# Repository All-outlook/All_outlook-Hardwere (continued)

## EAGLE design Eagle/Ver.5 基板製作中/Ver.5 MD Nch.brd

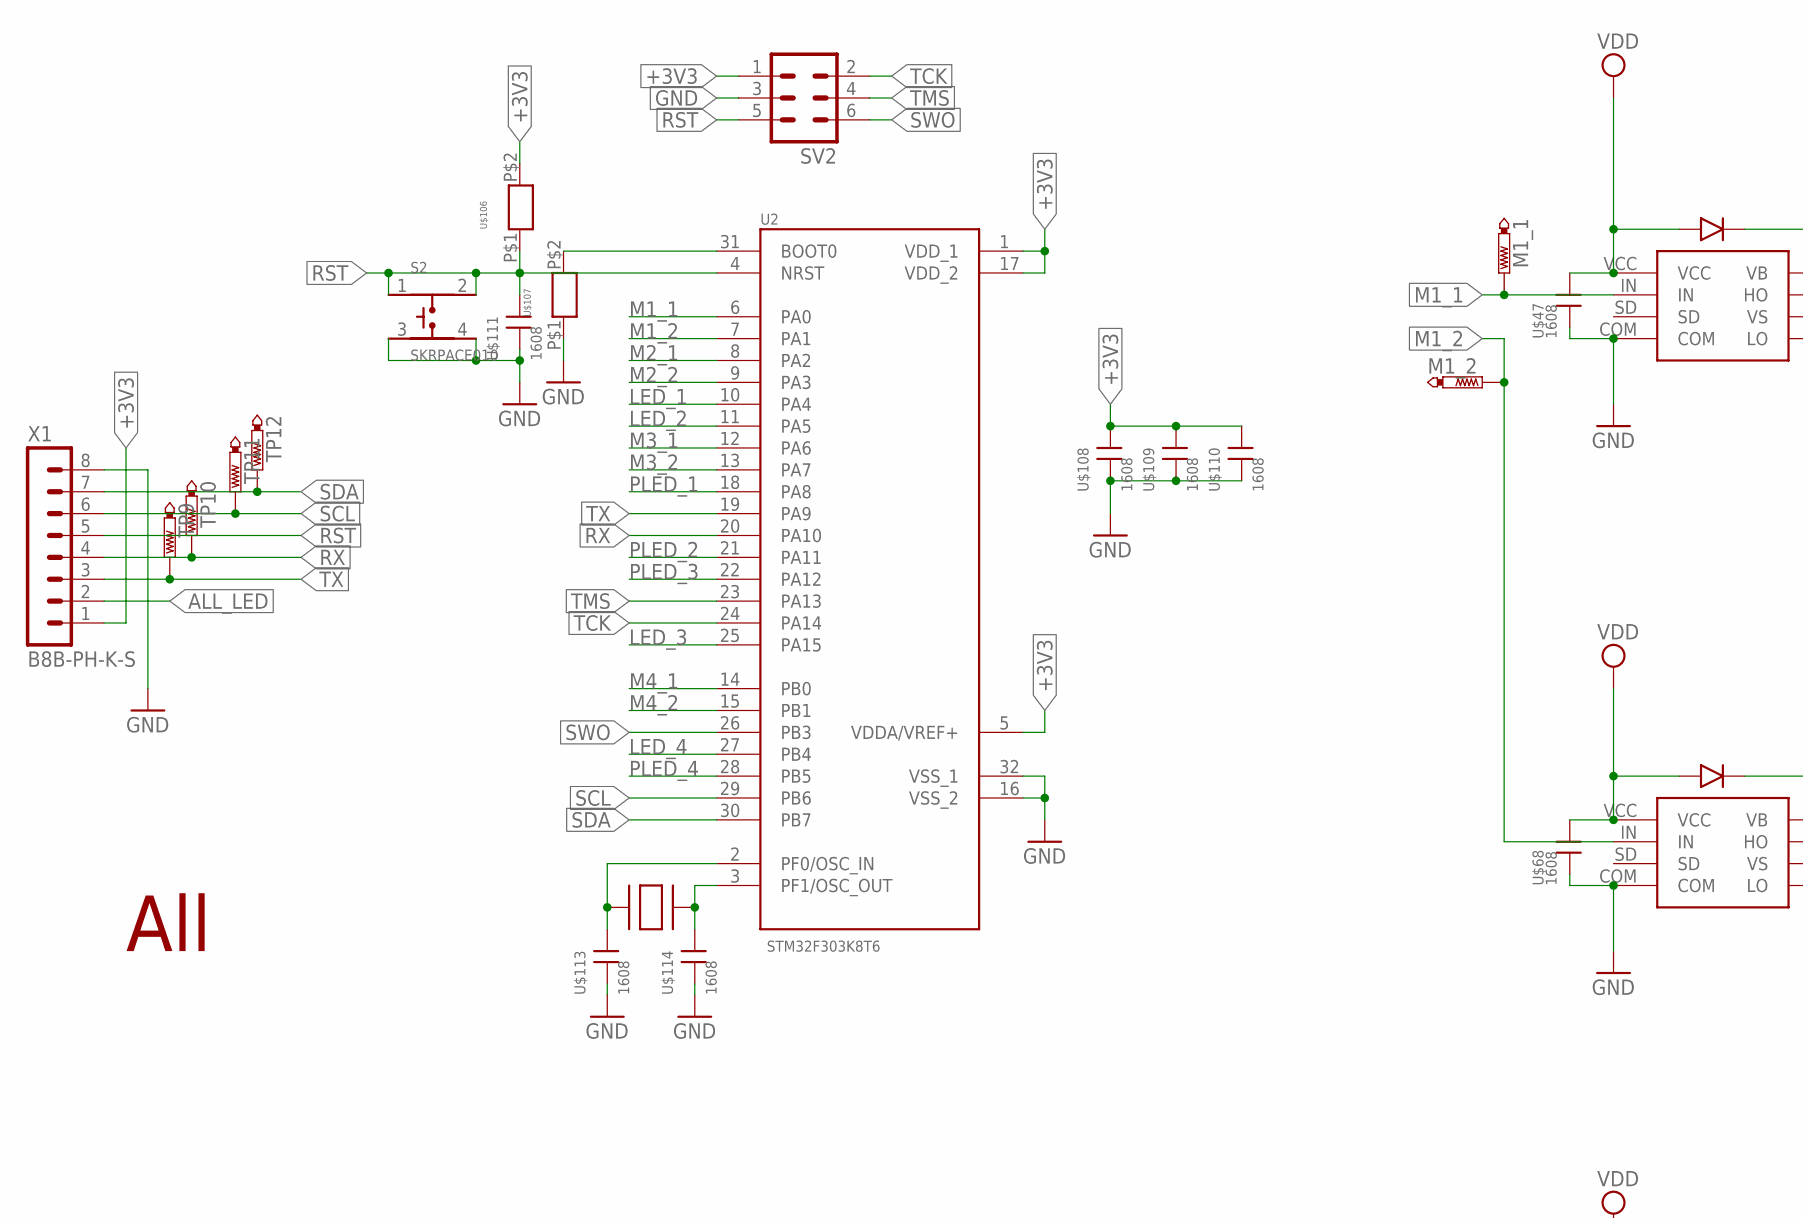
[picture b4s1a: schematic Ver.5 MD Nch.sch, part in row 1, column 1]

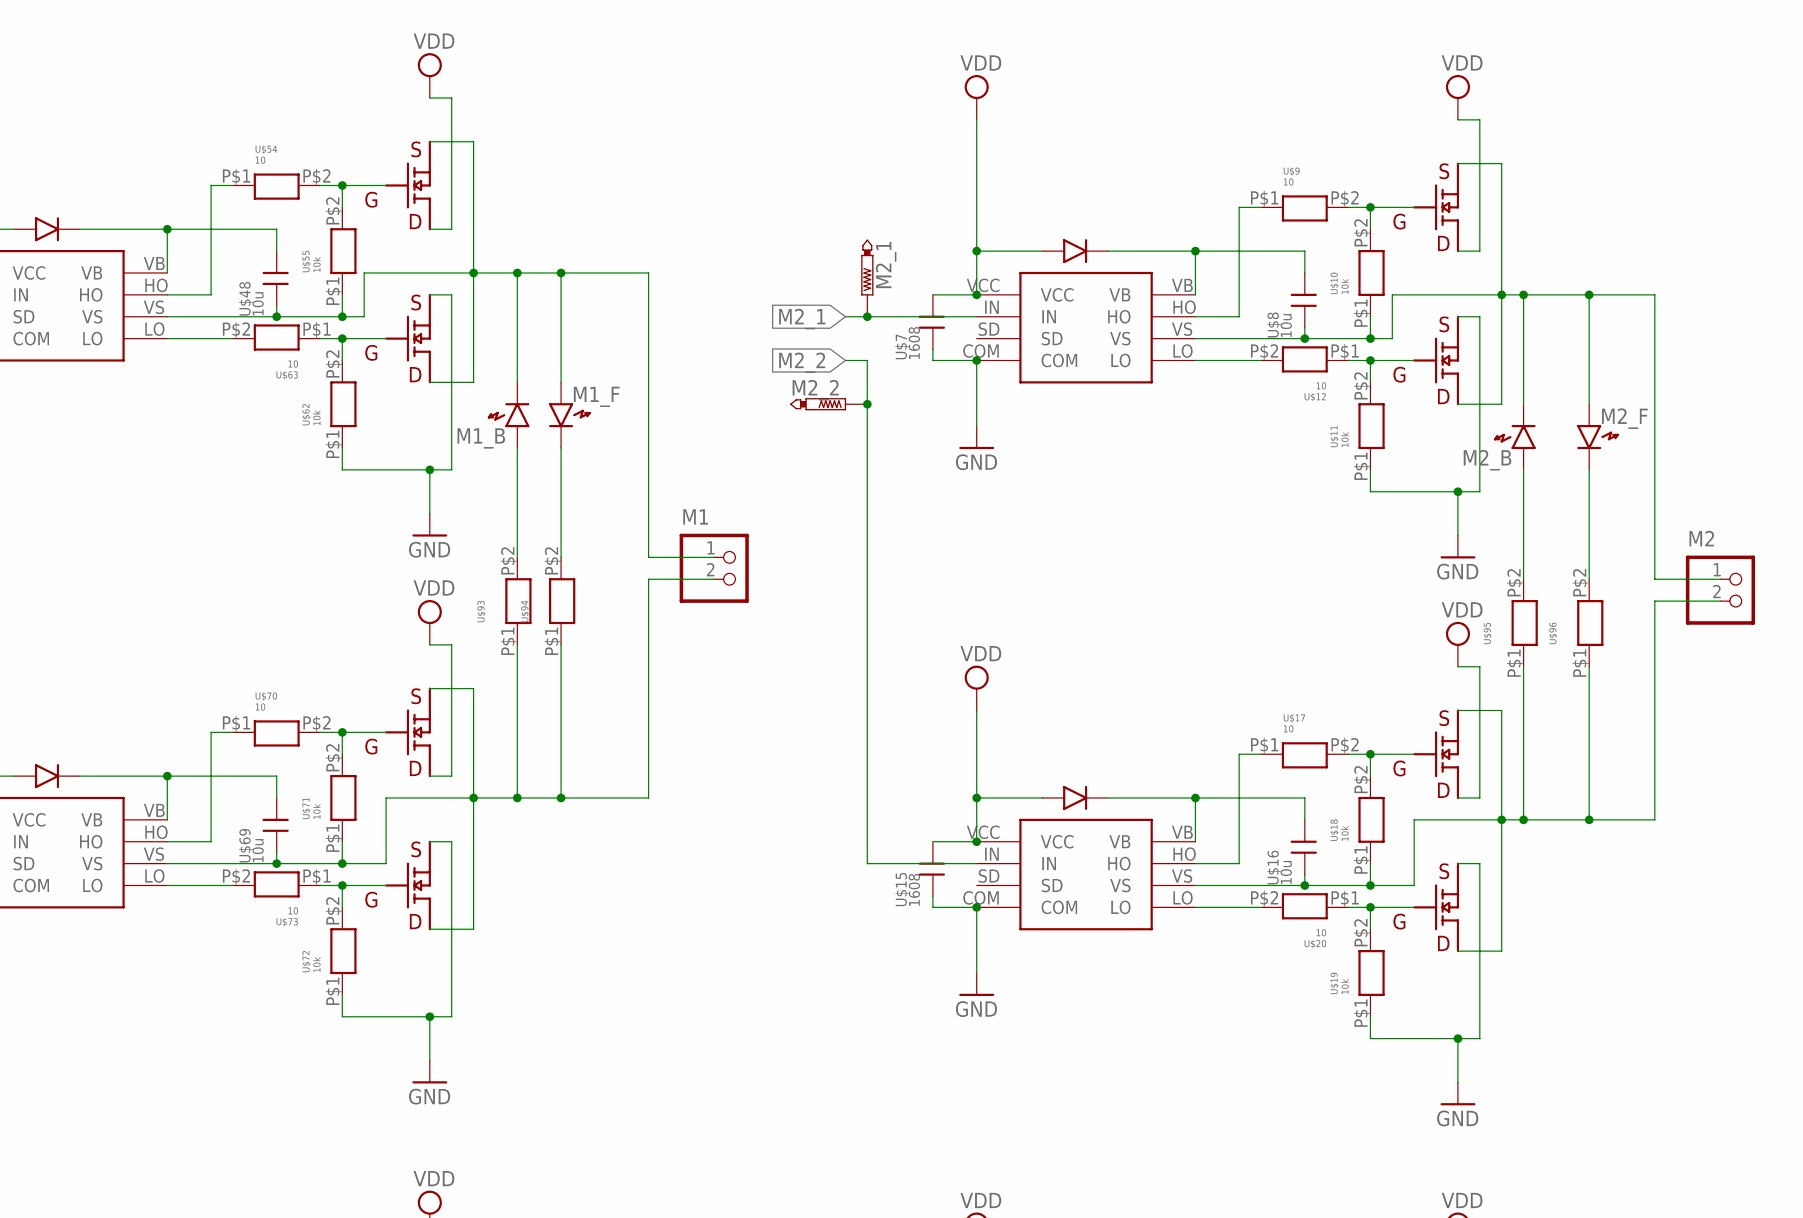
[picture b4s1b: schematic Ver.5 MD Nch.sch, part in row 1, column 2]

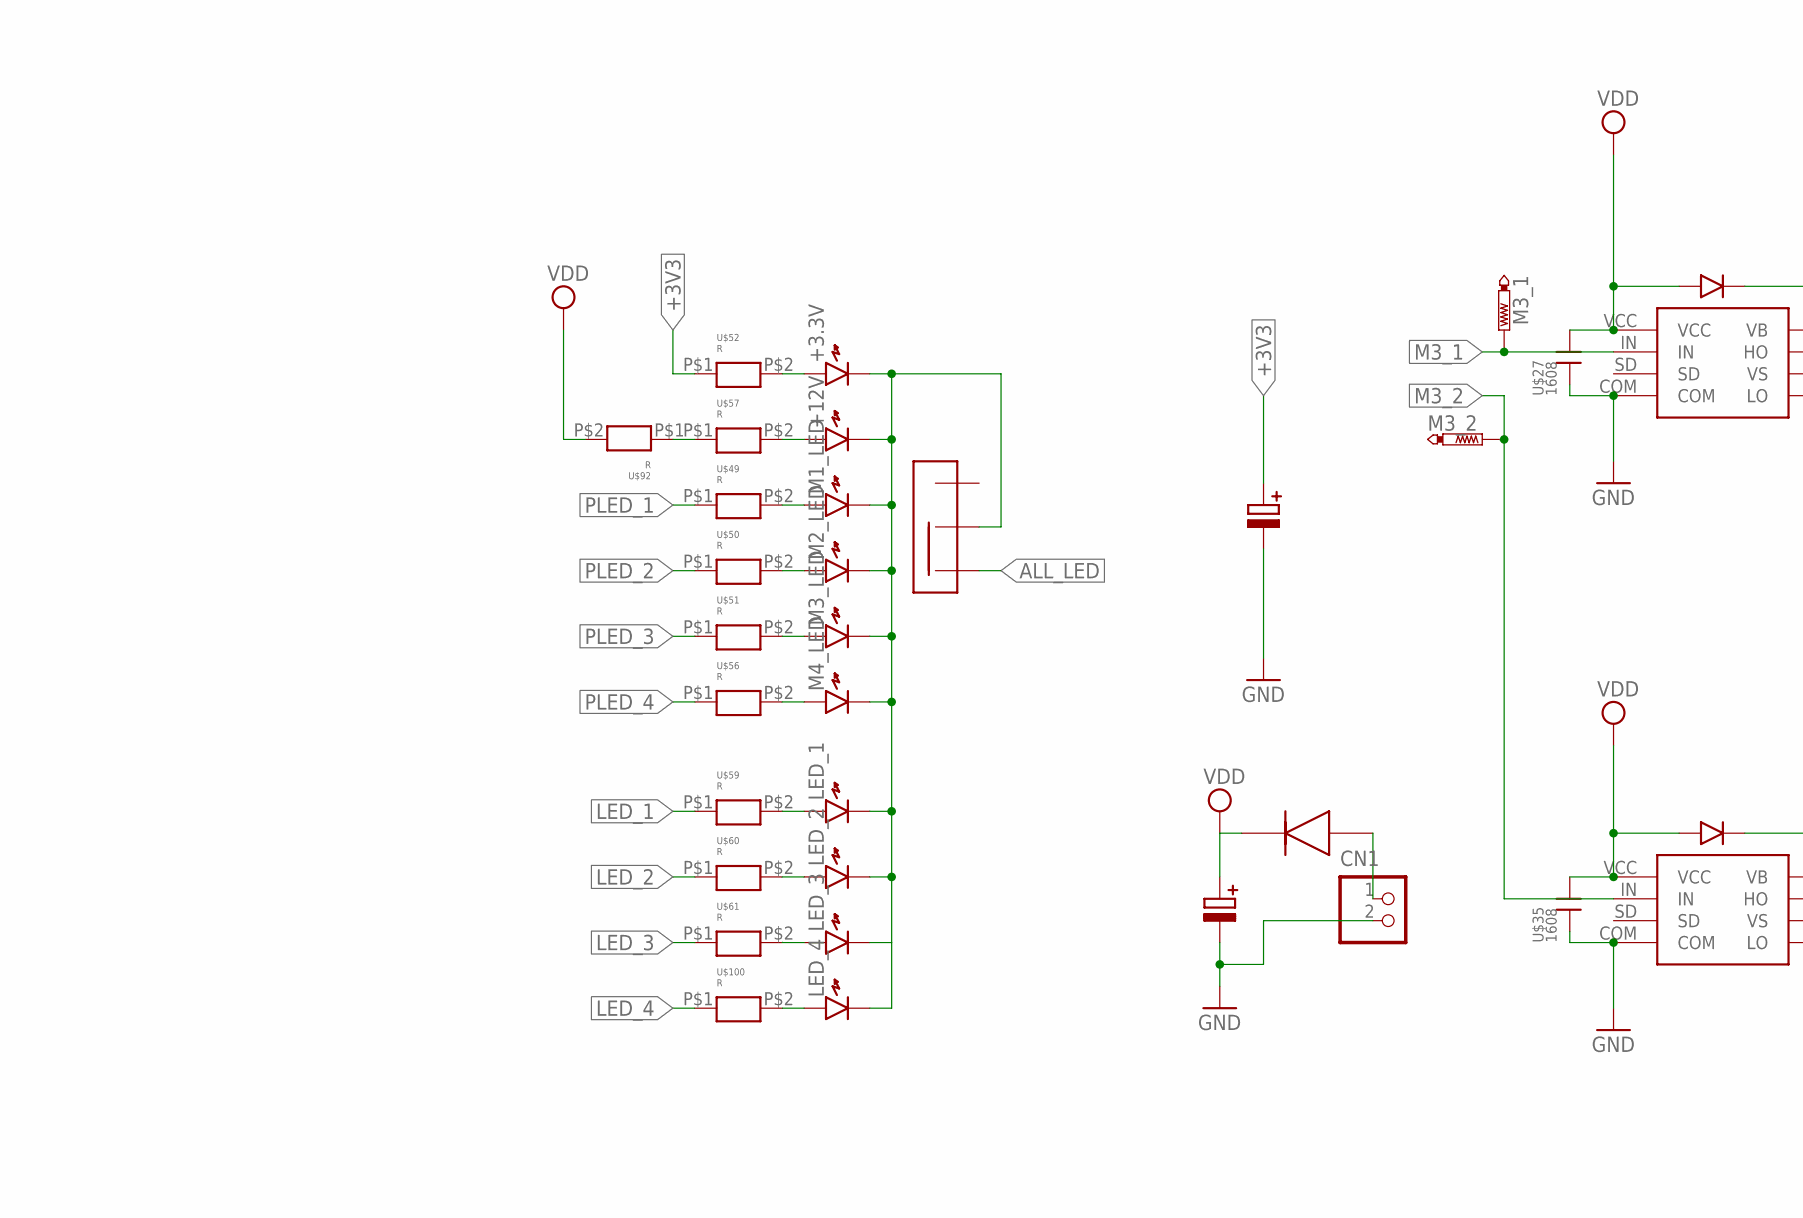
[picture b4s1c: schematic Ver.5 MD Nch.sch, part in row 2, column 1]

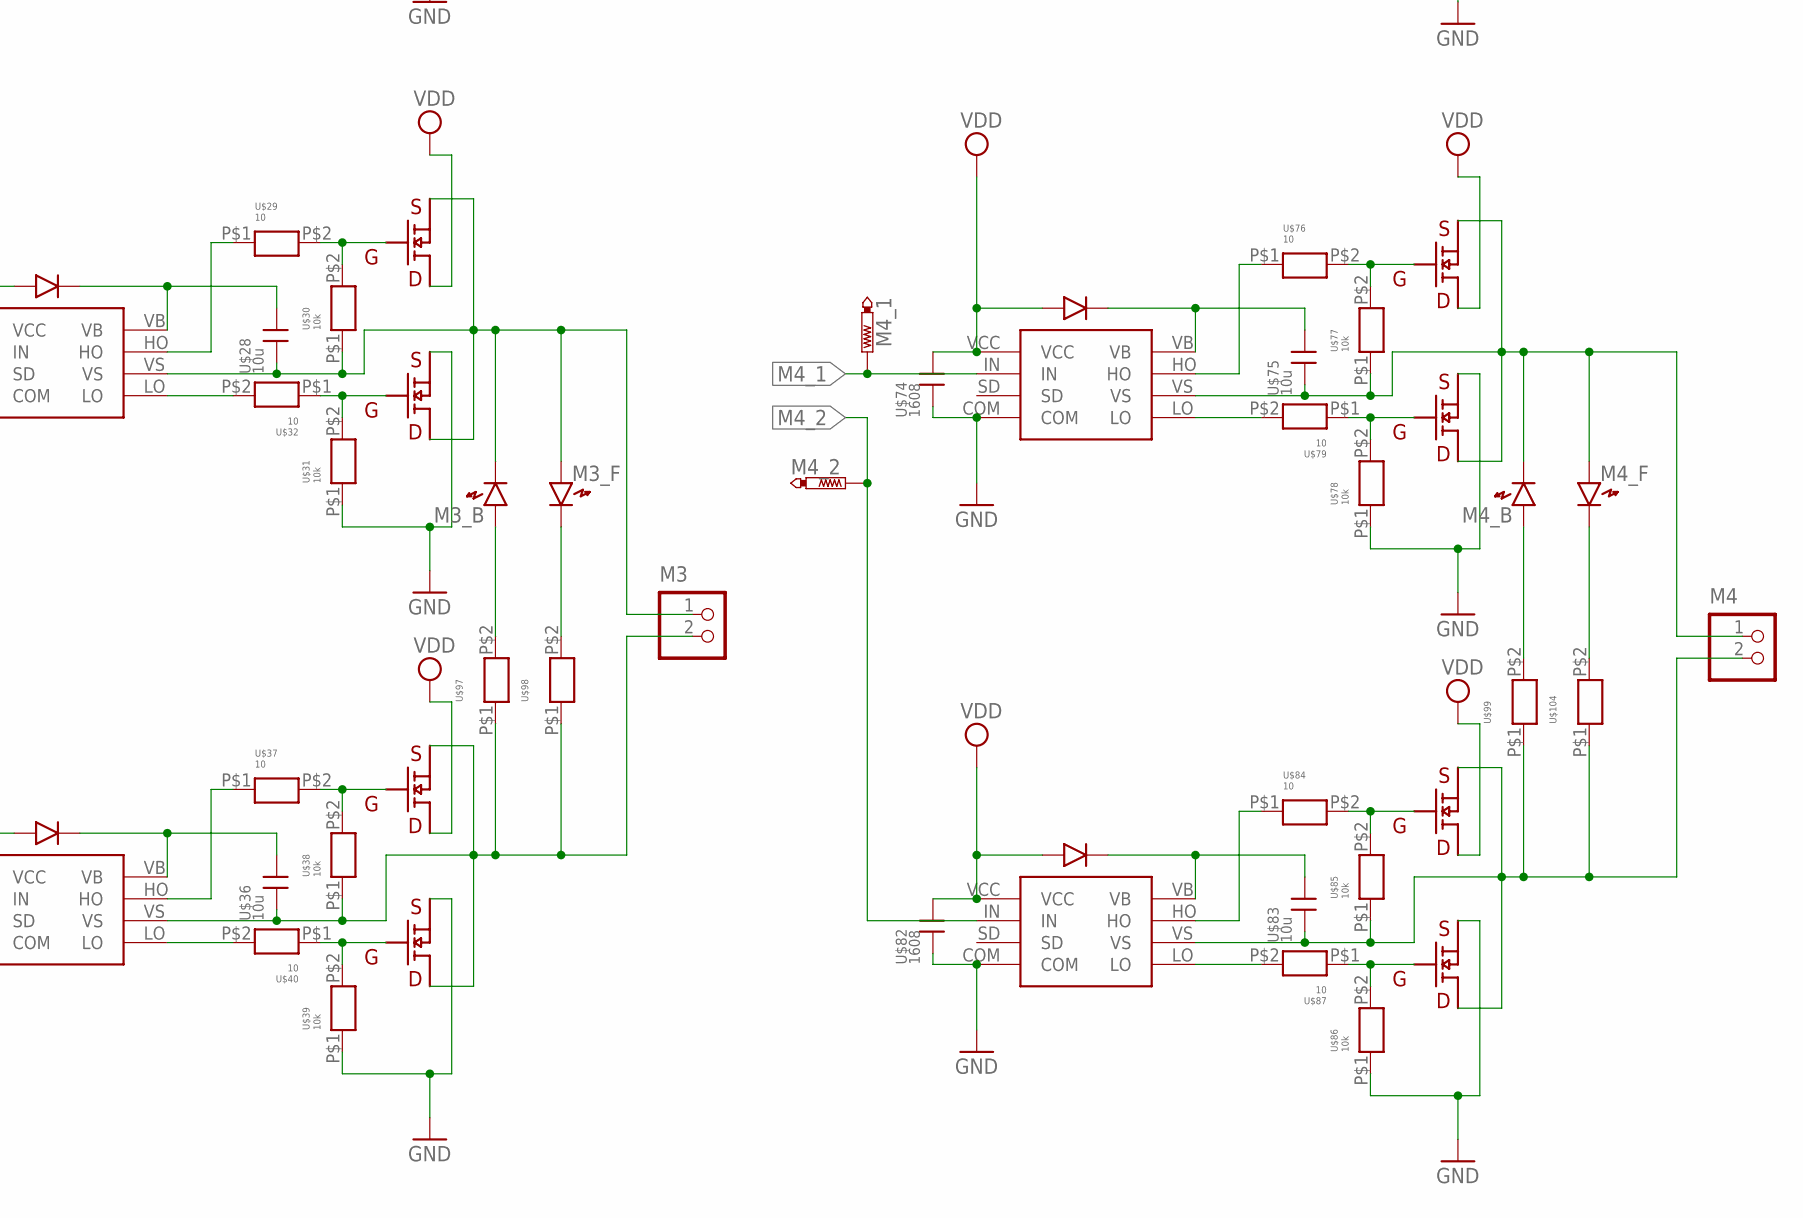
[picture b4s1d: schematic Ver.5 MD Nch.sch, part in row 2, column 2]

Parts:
+3.3V, +12V: LED1608
CN1: B2B-XH-A
LED_1, LED_2, LED_3, LED_4: LED1608
M1, M2, M3, M4: S2B-XH-A
M1_1, M1_2, M2_1, M2_2, M3_1, M3_2, M4_1, M4_2: PTR1B1,27; B1,27
M1_B, M1_F, M1_LED, M2_B, M2_F, M2_LED, M3_B, M3_F, M3_LED, M4_B, M4_F, M4_LED: LED1608
S2: SKRPACE010; SW_SKRPACE010
SV2: ML6
TP9, TP10, TP11, TP12: PTR1B1,27; B1,27
U2: STM32F303K8T6; QFP80P900X900X160-32N
U$1, U$2, U$3, U$4, U$21, U$22, U$23, U$24, U$41, U$42, U$43, U$44, U$88, U$89, U$90, U$91: SSM6K8
U$5, U$13, U$25, U$33, U$45, U$64, U$66, U$80: IR2302
U$6, U$14, U$26, U$34, U$46, U$65, U$67, U$81: 1N4148
U$7, U$15, U$27, U$35, U$47, U$68, U$74, U$82, U$108, U$109, U$110, U$111, U$113, U$114: 1608; CON
U$8, U$16, U$28, U$36, U$48, U$69, U$75, U$83: 10u; CON
U$9, U$12, U$17, U$20, U$29, U$32, U$37, U$40, U$54, U$63, U$70, U$73, U$76, U$79, U$84, U$87: 10; 1608
U$10, U$11, U$18, U$19, U$30, U$31, U$38, U$39, U$55, U$62, U$71, U$72, U$77, U$78, U$85, U$86: 10k; 1608
U$49, U$50, U$51, U$52, U$56, U$57, U$59, U$60, U$61, U$92, U$93, U$94, U$95, U$96, U$97, U$98, U$99, U$100, U$104, U$106, U$107: R; 1608
U$53: SSW
U$58, U$101: 25V100
U$102: 40V5A
U$103: ALL
U$112: SUISYOU; 水晶
X1: B8B-PH-K-S

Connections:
+3V3: SV2.1, U2.1 (VDD_1), U2.5 (VDDA/VREF+), U2.17 (VDD_2), U$52.P$1, U$58.P$1, U$106.P$2, U$108.P$1 (1), U$109.P$1 (1), U$110.P$1 (1), X1.1
ALL_LED: U$53.P$1, X1.2
GND: CN1.2, S2.3, S2.4, SV2.3, U2.16 (VSS_2), U2.32 (VSS_1), U$2.S, U$4.S, U$5.COM, U$7.P$2 (2), U$11.P$1, U$13.COM, U$15.P$2 (2), U$19.P$1, U$22.S, U$24.S, U$25.COM, U$27.P$2 (2), U$31.P$1, U$33.COM, U$35.P$2 (2), U$39.P$1, U$42.S, U$44.S, U$45.COM, U$47.P$2 (2), U$58.P$2, U$62.P$1, U$64.COM, U$66.COM, U$68.P$2 (2), U$72.P$1, U$74.P$2 (2), U$78.P$1, U$80.COM, U$82.P$2 (2), U$86.P$1, U$89.S, U$91.S, U$101.P$2, U$107.P$1, U$108.P$2 (2), U$109.P$2 (2), U$110.P$2 (2), U$111.P$2 (2), U$113.P$2 (2), U$114.P$2 (2), X1.8
LED_1: U2.10 (PA4), U$59.P$1
LED_2: U2.11 (PA5), U$60.P$1
LED_3: U2.25 (PA15), U$61.P$1
LED_4: U2.27 (PB4), U$100.P$1
M1_1: M1_1.TP, U2.6 (PA0), U$45.IN
M1_2: M1_2.TP, U2.7 (PA1), U$66.IN
M2_1: M2_1.TP, U2.8 (PA2), U$5.IN
M2_2: M2_2.TP, U2.9 (PA3), U$13.IN
M3_1: M3_1.TP, U2.12 (PA6), U$25.IN
M3_2: M3_2.TP, U2.13 (PA7), U$33.IN
M4_1: M4_1.TP, U2.14 (PB0), U$64.IN
M4_2: M4_2.TP, U2.15 (PB1), U$80.IN
unnamed: M1.2, U$3.S, U$4.D, U$4.DD (D), U$4.DDD (D), U$4.DDDD (D), U$66.VS, U$69.P$2 (2), U$71.P$1, U$93.P$1, U$94.P$1
unnamed: U$5.VB, U$6.P$2, U$8.P$1 (1)
unnamed: M2.1, M2_B.K, M2_F.A, U$5.VS, U$8.P$2 (2), U$10.P$1, U$21.S, U$22.D, U$22.DD (D), U$22.DDD (D), U$22.DDDD (D)
unnamed: U$9.P$2, U$10.P$2, U$21.G
unnamed: M1_LED.A, U$49.P$2
unnamed: U$5.HO, U$9.P$1
unnamed: U$5.LO, U$12.P$2
unnamed: U$11.P$2, U$12.P$1, U$22.G
unnamed: U$13.VB, U$14.P$2, U$16.P$1 (1)
unnamed: U$17.P$2, U$18.P$2, U$23.G
unnamed: U$13.HO, U$17.P$1
unnamed: U$13.LO, U$20.P$2
unnamed: U$19.P$2, U$20.P$1, U$24.G
unnamed: M2.2, U$13.VS, U$16.P$2 (2), U$18.P$1, U$23.S, U$24.D, U$24.DD (D), U$24.DDD (D), U$24.DDDD (D), U$95.P$1, U$96.P$1
unnamed: U$25.VB, U$26.P$2, U$28.P$1 (1)
unnamed: M3.1, M3_B.K, M3_F.A, U$25.VS, U$28.P$2 (2), U$30.P$1, U$41.S, U$42.D, U$42.DD (D), U$42.DDD (D), U$42.DDDD (D)
unnamed: U$29.P$2, U$30.P$2, U$41.G
unnamed: M2_LED.A, U$50.P$2
unnamed: U$25.HO, U$29.P$1
unnamed: U$25.LO, U$32.P$2
unnamed: M3_LED.A, U$51.P$2
unnamed: U$31.P$2, U$32.P$1, U$42.G
unnamed: U$33.VB, U$34.P$2, U$36.P$1 (1)
unnamed: U$37.P$2, U$38.P$2, U$43.G
unnamed: U$33.HO, U$37.P$1
unnamed: U$33.LO, U$40.P$2
unnamed: U$39.P$2, U$40.P$1, U$44.G
unnamed: +3.3V.A, U$52.P$2
unnamed: CN1.1, U$102.P$1
unnamed: +12V.A, U$57.P$2
unnamed: M3.2, U$33.VS, U$36.P$2 (2), U$38.P$1, U$43.S, U$44.D, U$44.DD (D), U$44.DDD (D), U$44.DDDD (D), U$97.P$1, U$98.P$1
unnamed: U$64.VB, U$65.P$2, U$75.P$1 (1)
unnamed: LED_1.A, U$59.P$2
unnamed: M4_LED.A, U$56.P$2
unnamed: U$45.VB, U$46.P$2, U$48.P$1 (1)
unnamed: M1.1, M1_B.K, M1_F.A, U$1.S, U$2.D, U$2.DD (D), U$2.DDD (D), U$2.DDDD (D), U$45.VS, U$48.P$2 (2), U$55.P$1
unnamed: LED_3.A, U$61.P$2
unnamed: LED_2.A, U$60.P$2
unnamed: U$1.G, U$54.P$2, U$55.P$2
unnamed: U$45.HO, U$54.P$1
unnamed: U$45.LO, U$63.P$2
unnamed: U$2.G, U$62.P$2, U$63.P$1
unnamed: U$66.VB, U$67.P$2, U$69.P$1 (1)
unnamed: M4.1, M4_B.K, M4_F.A, U$64.VS, U$75.P$2 (2), U$77.P$1, U$88.S, U$89.D, U$89.DD (D), U$89.DDD (D), U$89.DDDD (D)
unnamed: U$3.G, U$70.P$2, U$71.P$2
unnamed: U$66.HO, U$70.P$1
unnamed: U$66.LO, U$73.P$2
unnamed: U$4.G, U$72.P$2, U$73.P$1
unnamed: U$76.P$2, U$77.P$2, U$88.G
unnamed: U$64.HO, U$76.P$1
unnamed: U$64.LO, U$79.P$2
unnamed: U$78.P$2, U$79.P$1, U$89.G
unnamed: U$80.VB, U$81.P$2, U$83.P$1 (1)
unnamed: U$84.P$2, U$85.P$2, U$90.G
unnamed: U$80.HO, U$84.P$1
unnamed: U$80.LO, U$87.P$2
unnamed: U$86.P$2, U$87.P$1, U$91.G
unnamed: M4.2, U$80.VS, U$83.P$2 (2), U$85.P$1, U$90.S, U$91.D, U$91.DD (D), U$91.DDD (D), U$91.DDDD (D), U$99.P$1, U$104.P$1
unnamed: U$57.P$1, U$92.P$1
unnamed: M1_B.A, U$93.P$2
unnamed: M1_F.K, U$94.P$2
unnamed: M2_B.A, U$95.P$2
unnamed: +3.3V.K, +12V.K, LED_1.K, LED_2.K, LED_3.K, LED_4.K, M1_LED.K, M2_LED.K, M3_LED.K, M4_LED.K, U$53.P$3
unnamed: LED_4.A, U$100.P$2
unnamed: M3_B.A, U$97.P$2
unnamed: M2_F.K, U$96.P$2
unnamed: M4_B.A, U$99.P$2
unnamed: M4_F.K, U$104.P$2
unnamed: M3_F.K, U$98.P$2
unnamed: U2.31 (BOOT0), U$107.P$2
unnamed: U2.2 (PF0/OSC_IN), U$112.P$1, U$113.P$1 (1)
unnamed: U2.3 (PF1/OSC_OUT), U$112.P$2, U$114.P$1 (1)
PLED_1: U2.18 (PA8), U$49.P$1
PLED_2: U2.21 (PA11), U$50.P$1
PLED_3: U2.22 (PA12), U$51.P$1
PLED_4: U2.28 (PB5), U$56.P$1
RST: S2.1, S2.2, SV2.5, U2.4 (NRST), U$106.P$1, U$111.P$1 (1), X1.5
RX: TP10.TP, U2.20 (PA10), X1.4
SCL: TP11.TP, U2.29 (PB6), X1.6
SDA: TP12.TP, U2.30 (PB7), X1.7
SWO: SV2.6, U2.26 (PB3)
TCK: SV2.2, U2.24 (PA14)
TMS: SV2.4, U2.23 (PA13)
TX: TP9.TP, U2.19 (PA9), X1.3
VDD: U$1.D, U$1.DD (D), U$1.DDD (D), U$1.DDDD (D), U$3.D, U$3.DD (D), U$3.DDD (D), U$3.DDDD (D), U$5.VCC, U$6.P$1, U$7.P$1 (1), U$13.VCC, U$14.P$1, U$15.P$1 (1), U$21.D, U$21.DD (D), U$21.DDD (D), U$21.DDDD (D), U$23.D, U$23.DD (D), U$23.DDD (D), U$23.DDDD (D), U$25.VCC, U$26.P$1, U$27.P$1 (1), U$33.VCC, U$34.P$1, U$35.P$1 (1), U$41.D, U$41.DD (D), U$41.DDD (D), U$41.DDDD (D), U$43.D, U$43.DD (D), U$43.DDD (D), U$43.DDDD (D), U$45.VCC, U$46.P$1, U$47.P$1 (1), U$64.VCC, U$65.P$1, U$66.VCC, U$67.P$1, U$68.P$1 (1), U$74.P$1 (1), U$80.VCC, U$81.P$1, U$82.P$1 (1), U$88.D, U$88.DD (D), U$88.DDD (D), U$88.DDDD (D), U$90.D, U$90.DD (D), U$90.DDD (D), U$90.DDDD (D), U$92.P$2, U$101.P$1, U$102.P$2

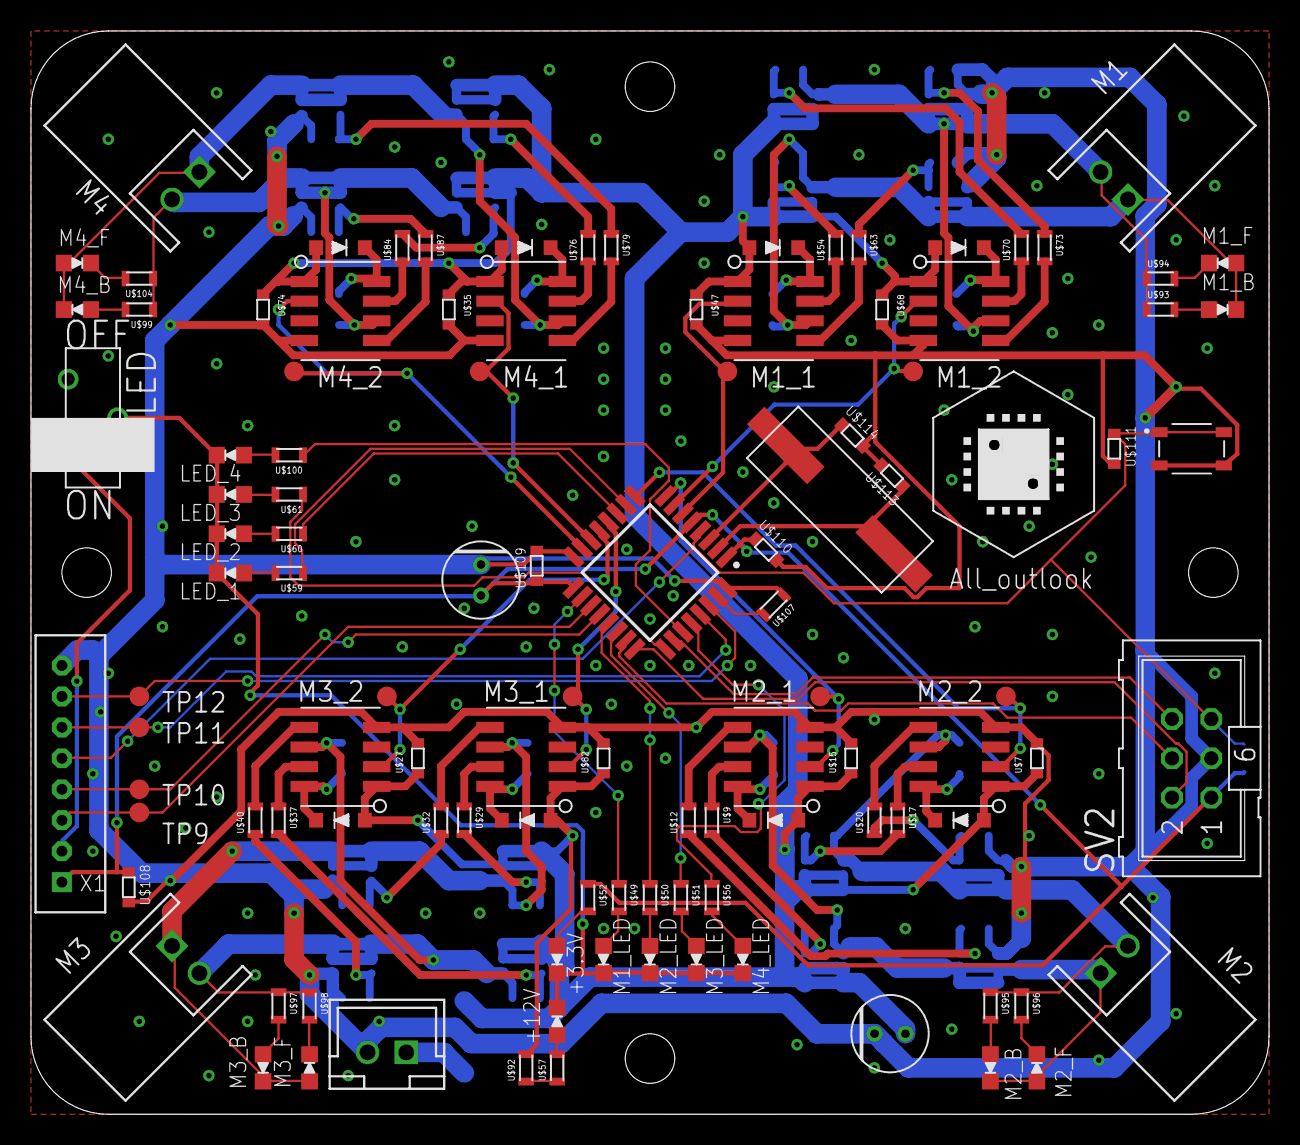
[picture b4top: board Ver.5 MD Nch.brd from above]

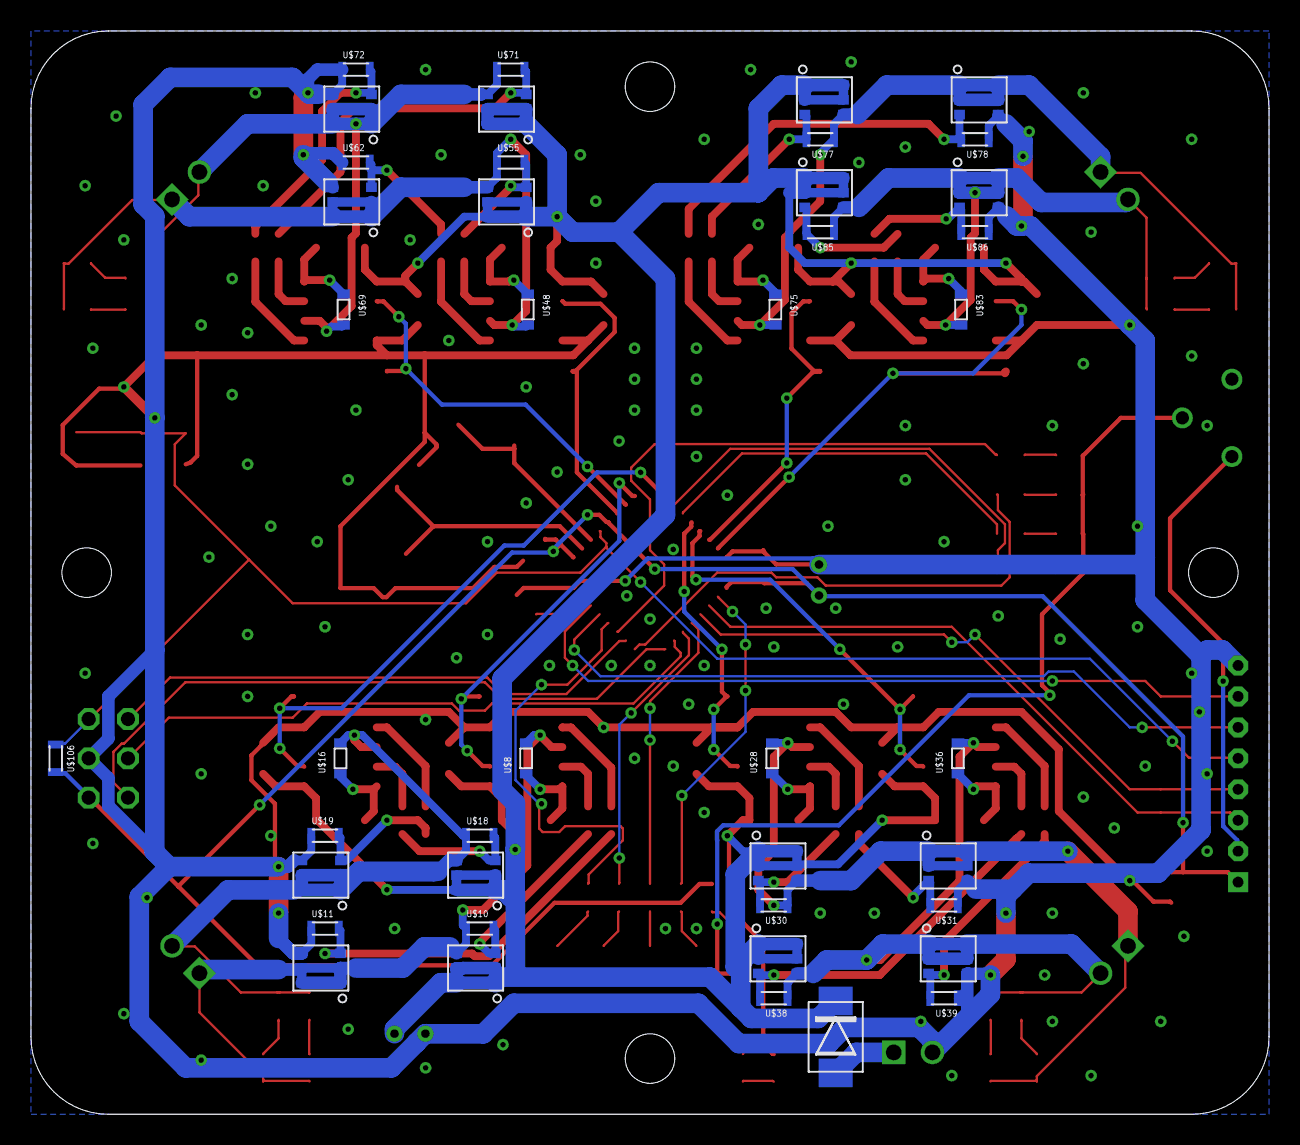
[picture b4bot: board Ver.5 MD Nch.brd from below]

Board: 2 copper layers, 80.0 x 70.0 mm, 152 parts (42 on the bottom side), 100 nets.

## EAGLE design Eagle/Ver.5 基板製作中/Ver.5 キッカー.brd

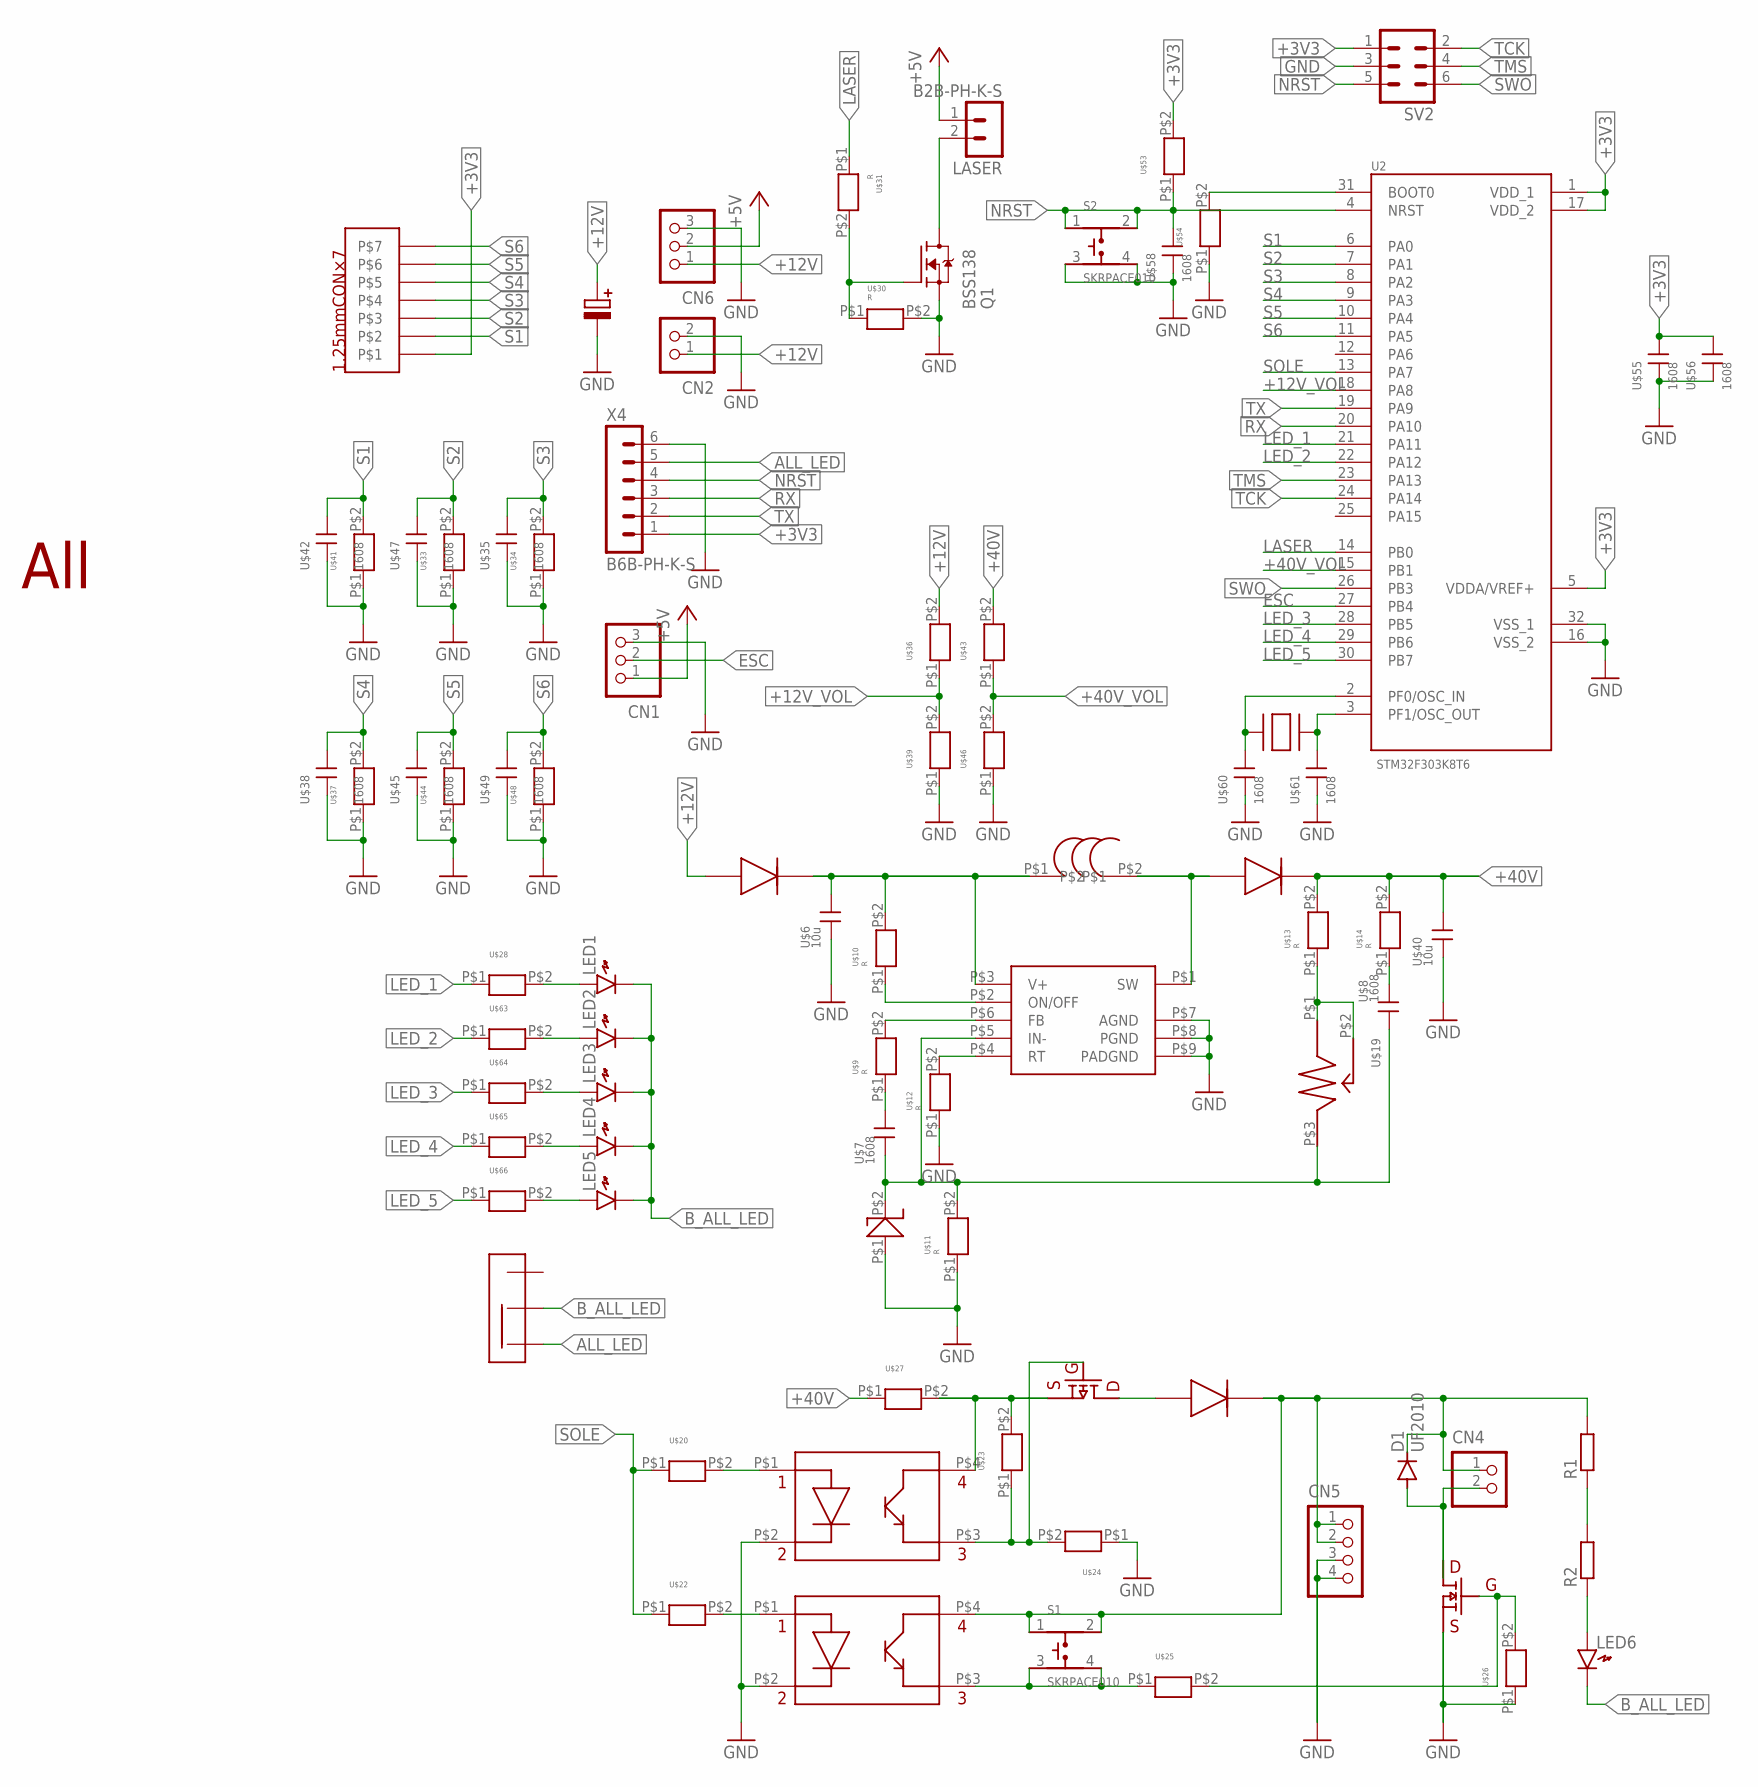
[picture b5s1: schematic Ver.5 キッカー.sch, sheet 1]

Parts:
CN1, CN6: B3B-XH-A
CN2, CN4: B2B-XH-A
CN5: B4B-XH-A
D1: UF2010; DO35-10
LASER: B2B-PH-K-S
LED1, LED2, LED3, LED4, LED5, LED6: LED1608
Q1: BSS138; SOT23
R1, R2: R-EU_0207/12; 0207/12
S1, S2: SKRPACE010; SW_SKRPACE010
SV2: ML6
U2: STM32F303K8T6; QFP80P900X900X160-32N
U$1: TD
U$2, U$3, U$18: 40V5A
U$4, U$15: TLP291; TPL291
U$5: NJW4131GM1; NJW4131
U$6, U$40: 10u; CON
U$7, U$8, U$35, U$38, U$42, U$45, U$47, U$49, U$55, U$56, U$58, U$60, U$61: 1608; CON
U$9, U$10, U$11, U$12, U$13, U$14, U$20, U$22, U$23, U$24, U$25, U$26, U$27, U$28, U$30, U$31, U$33, U$34, U$36, U$37, U$39, U$41, U$43, U$44, U$46, U$48, U$53, U$54, U$63, U$64, U$65, U$66: R; 1608
U$16: 808
U$17: SSM6K8
U$19: VR
U$21: 1MM7
U$29: ALL
U$50: I
U$59: SUISYOU; 水晶
U$62: 25V100
U$67: SSW
X4: B6B-PH-K-S

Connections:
+3V3: SV2.1, U2.1 (VDD_1), U2.5 (VDDA/VREF+), U2.17 (VDD_2), U$21.P$1, U$53.P$2, U$55.P$1 (1), U$56.P$1 (1), X4.1
+5V: CN1.1, CN6.2, LASER.1
+12V: CN2.1, CN6.1, U$3.P$1, U$36.P$2, U$62.P$1
+12V_VOL: U2.18 (PA8), U$36.P$1, U$39.P$2
+40V: U$2.P$2, U$13.P$2, U$14.P$2, U$27.P$1, U$40.P$1 (1), U$43.P$2
+40V_VOL: U2.15 (PB1), U$43.P$1, U$46.P$2
ALL_LED: U$67.P$1, X4.5
B_ALL_LED: LED1.K, LED2.K, LED3.K, LED4.K, LED5.K, LED6.K, U$67.P$3
ESC: CN1.2, U2.27 (PB4)
GND: CN1.3, CN2.2, CN5.3, CN5.4, CN6.3, Q1.2 (S), S2.3, S2.4, SV2.3, U2.16 (VSS_2), U2.32 (VSS_1), U$1.P$1, U$4.P$2 (2), U$5.P$7 (AGND), U$5.P$8 (PGND), U$5.P$9 (PADGND), U$6.P$2 (2), U$11.P$1, U$12.P$1, U$15.P$2 (2), U$17.S, U$24.P$1, U$26.P$1, U$30.P$2, U$33.P$1, U$34.P$1, U$35.P$2 (2), U$37.P$1, U$38.P$2 (2), U$39.P$1, U$40.P$2 (2), U$41.P$1, U$42.P$2 (2), U$44.P$1, U$45.P$2 (2), U$46.P$1, U$47.P$2 (2), U$48.P$1, U$49.P$2 (2), U$54.P$1, U$55.P$2 (2), U$56.P$2 (2), U$58.P$2 (2), U$60.P$2 (2), U$61.P$2 (2), U$62.P$2, X4.6
LASER: U2.14 (PB0), U$31.P$1
LED_1: U2.21 (PA11), U$28.P$1
LED_2: U2.22 (PA12), U$63.P$1
LED_3: U2.28 (PB5), U$64.P$1
LED_4: U2.29 (PB6), U$65.P$1
LED_5: U2.30 (PB7), U$66.P$1
unnamed: U$4.P$1 (1), U$20.P$2
unnamed: U$5.P$2 (ON/OFF), U$10.P$1
unnamed: U$1.P$2, U$5.P$5 (IN-), U$7.P$2 (2), U$8.P$2 (2), U$11.P$2, U$19.P$3
unnamed: U$8.P$1 (1), U$14.P$1
unnamed: U$3.P$2, U$5.P$3 (V+), U$6.P$1 (1), U$10.P$2, U$50.P$1
unnamed: U$2.P$1, U$5.P$1 (SW), U$50.P$2
unnamed: U$5.P$6 (FB), U$9.P$2
unnamed: U$7.P$1 (1), U$9.P$1
unnamed: U$15.P$1 (1), U$22.P$2
unnamed: U$5.P$4 (RT), U$12.P$2
unnamed: LED6.A, R2.1
unnamed: U$4.P$4 (4), U$16.S, U$23.P$2, U$27.P$2
unnamed: U$4.P$3 (3), U$16.G, U$23.P$1, U$24.P$2
unnamed: S1.3, S1.4, U$15.P$3 (3), U$25.P$1
unnamed: U$17.G, U$25.P$2, U$26.P$2
unnamed: R1.1, R2.2
unnamed: CN4.2, D1.A, U$17.D, U$17.DD (D), U$17.DDD (D), U$17.DDDD (D)
unnamed: CN4.1, CN5.1, CN5.2, D1.C, R1.2, S1.1, S1.2, U$15.P$4 (4), U$18.P$2
unnamed: U$16.D, U$16.DD (D), U$16.DDD (D), U$16.DDDD (D), U$18.P$1
unnamed: LASER.2, Q1.3 (D)
unnamed: Q1.1 (G), U$30.P$1, U$31.P$2
unnamed: LED2.A, U$63.P$2
unnamed: U$13.P$1, U$19.P$1, U$19.P$2
unnamed: LED1.A, U$28.P$2
unnamed: LED3.A, U$64.P$2
unnamed: LED4.A, U$65.P$2
unnamed: LED5.A, U$66.P$2
unnamed: U2.31 (BOOT0), U$54.P$2
unnamed: U2.2 (PF0/OSC_IN), U$59.P$1, U$60.P$1 (1)
unnamed: U2.3 (PF1/OSC_OUT), U$59.P$2, U$61.P$1 (1)
NRST: S2.1, S2.2, SV2.5, U2.4 (NRST), U$53.P$1, U$58.P$1 (1), X4.4
RX: U2.20 (PA10), X4.3
S1: U2.6 (PA0), U$21.P$2, U$41.P$2, U$42.P$1 (1)
S2: U2.7 (PA1), U$21.P$3, U$33.P$2, U$47.P$1 (1)
S3: U2.8 (PA2), U$21.P$4, U$34.P$2, U$35.P$1 (1)
S4: U2.9 (PA3), U$21.P$5, U$37.P$2, U$38.P$1 (1)
S5: U2.10 (PA4), U$21.P$6, U$44.P$2, U$45.P$1 (1)
S6: U2.11 (PA5), U$21.P$7, U$48.P$2, U$49.P$1 (1)
SOLE: U2.13 (PA7), U$20.P$1, U$22.P$1
SWO: SV2.6, U2.26 (PB3)
TCK: SV2.2, U2.24 (PA14)
TMS: SV2.4, U2.23 (PA13)
TX: U2.19 (PA9), X4.2

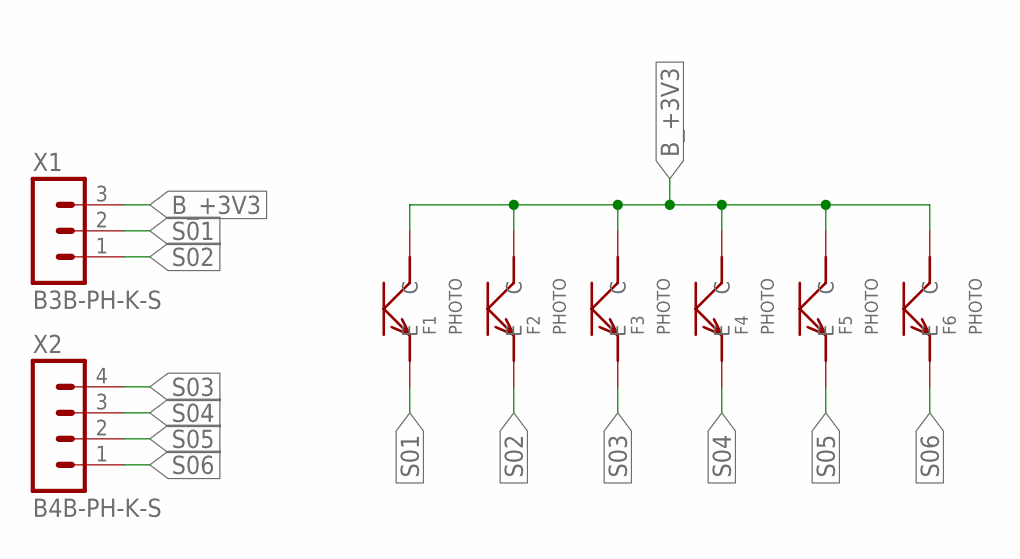
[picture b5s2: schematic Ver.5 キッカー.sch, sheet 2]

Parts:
F1, F2, F3, F4, F5, F6: PHOTO
X1: B3B-PH-K-S
X2: B4B-PH-K-S

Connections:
B_+3V3: F1.P$1 (C), F2.P$1 (C), F3.P$1 (C), F4.P$1 (C), F5.P$1 (C), F6.P$1 (C), X1.3
S01: F1.P$2 (E), X1.2
S02: F2.P$2 (E), X1.1
S03: F3.P$2 (E), X2.4
S04: F4.P$2 (E), X2.3
S05: F5.P$2 (E), X2.2
S06: F6.P$2 (E), X2.1
